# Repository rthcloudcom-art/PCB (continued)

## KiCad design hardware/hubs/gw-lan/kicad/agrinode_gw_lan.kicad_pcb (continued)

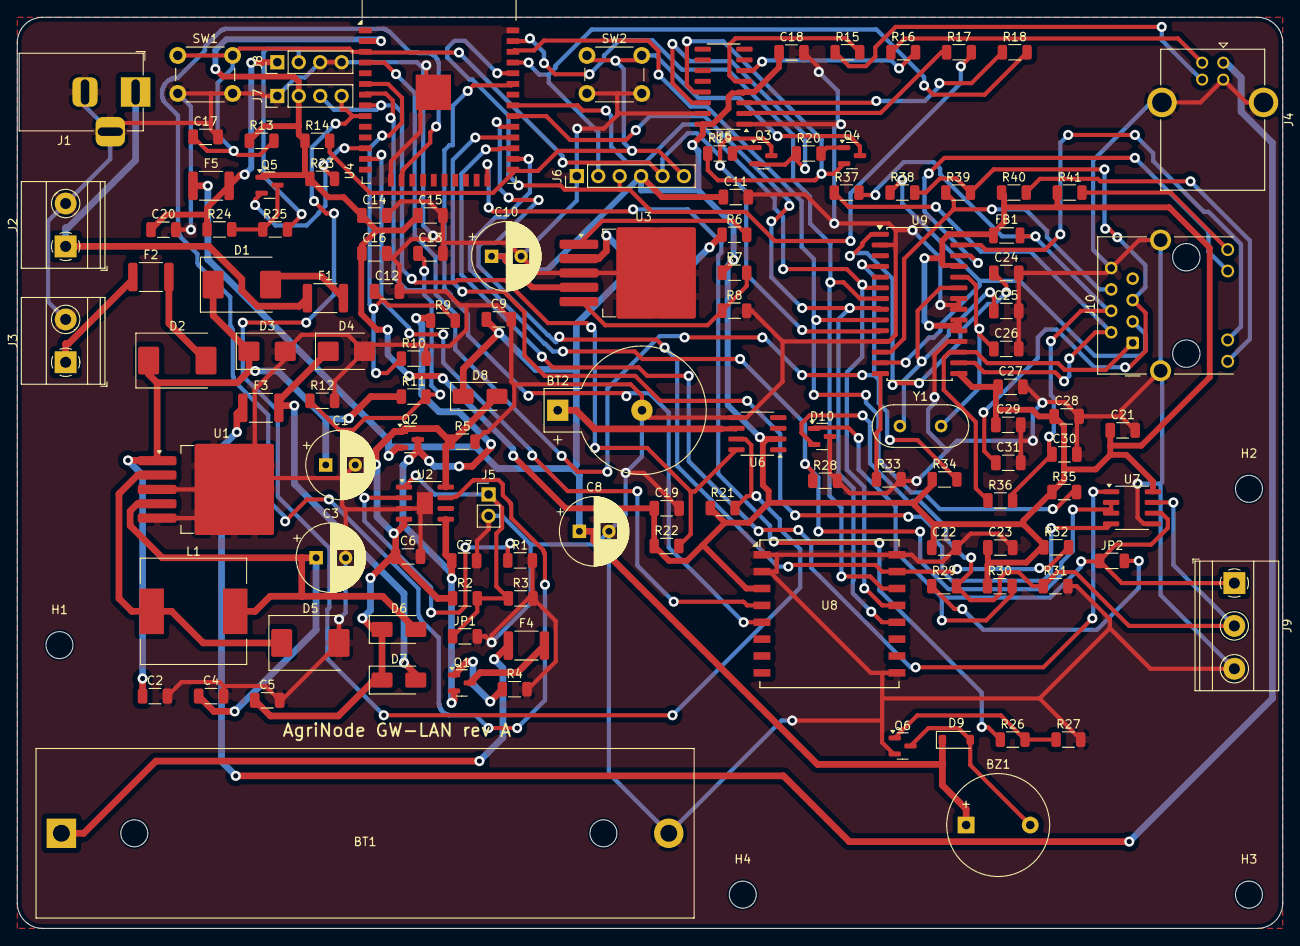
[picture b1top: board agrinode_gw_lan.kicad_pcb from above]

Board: 2 copper layers, 150.0 x 108.0 mm, 126 parts (0 on the bottom side), 76 nets.

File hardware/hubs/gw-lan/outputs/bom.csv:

Qty,Value,Footprint,Symbol,Option,References
1,18650 Li-ion (protected),BatteryHolder_MPD_BH-18650-PC2,Device:Battery_Cell,CORE,BT1
1,CR2032,BatteryHolder_Keystone_500,Device:Battery_Cell,CORE,BT2
1,5V magnetic buzzer,Buzzer_12x9.5RM7.6,Device:Buzzer,CORE,BZ1
1,220u/35V,CP_Radial_D8.0mm_P3.50mm,Device:C_Polarized,CORE,C1
1,1u/50V,C_1206_3216Metric,Device:C,CORE,C2
2,220u/10V,CP_Radial_D8.0mm_P3.50mm,Device:C_Polarized,CORE,C3 C8
3,1u,C_1206_3216Metric,Device:C,CORE,C4 C11 C17
7,10u,C_1206_3216Metric,Device:C,CORE,C5 C6 C7 C9 C22 C24 C27
1,100u/10V,CP_Radial_D8.0mm_P3.50mm,Device:C_Polarized,CORE,C10
11,100n,C_1206_3216Metric,Device:C,CORE,C12 C13 C15 C16 C18 C19 C23 C28 C29 C30 C31
2,22u,C_1206_3216Metric,Device:C,CORE,C14 C20
1,100n,C_1206_3216Metric,Device:C,RS485,C21
2,18p,C_1206_3216Metric,Device:C,CORE,C25 C26
3,SS54 40V/5A,D_SMC,Device:D_Schottky,CORE,D1 D2 D5
1,SMBJ24CA,D_SMB,Device:D_TVS,CORE,D3
1,SMBJ6.0CA,D_SMB,Device:D_TVS,CORE,D4
3,SS34,D_SMA,Device:D_Schottky,CORE,D6 D7 D8
1,1N4148W,D_SOD-123,Device:D,CORE,D9
1,SM712,SOT-23,Diode:SM712_SOT23,RS485,D10
2,PTC 1.5A/30V,Fuse_1812_4532Metric,Device:Polyfuse,CORE,F1 F2
1,PTC 1.5A/8V,Fuse_1812_4532Metric,Device:Polyfuse,CORE,F3
1,PTC 3A/16V,Fuse_1812_4532Metric,Device:Polyfuse,CORE,F4
1,PTC 0.75A/16V,Fuse_1812_4532Metric,Device:Polyfuse,CORE,F5
1,600R@100MHz,L_1206_3216Metric,Device:FerriteBead_Small,CORE,FB1
4,M3,MountingHole_3.2mm_M3,Mechanical:MountingHole,CORE,H1 H2 H3 H4
1,DC 12V 5.5/2.1,BarrelJack_Horizontal,Connector:Barrel_Jack_Switch,CORE,J1
1,DC IN 7-24V,"TerminalBlock_Phoenix_MKDS-1,5-2-5.08_1x02_P5.08mm_Horizontal",Connector:Screw_Terminal_01x02,CORE,J2
1,SOLAR 6-24V,"TerminalBlock_Phoenix_MKDS-1,5-2-5.08_1x02_P5.08mm_Horizontal",Connector:Screw_Terminal_01x02,CORE,J3
1,USB 5V / PROG,USB_B_THT_Coarse,Connector:USB_B,CORE,J4
1,BAT NTC 10k,PinHeader_1x02_P2.54mm_Vertical,Connector_Generic:Conn_01x02,CORE,J5
1,PROG,PinHeader_1x06_P2.54mm_Vertical,Connector_Generic:Conn_01x06,CORE,J6
1,I2C,PinHeader_1x04_P2.54mm_Vertical,Connector_Generic:Conn_01x04,CORE,J7
1,LED STRIP WS2813,PinHeader_1x04_P2.54mm_Vertical,Connector_Generic:Conn_01x04,CORE,J8
1,RS-485,"TerminalBlock_Phoenix_MKDS-1,5-3-5.08_1x03_P5.08mm_Horizontal",Connector:Screw_Terminal_01x03,RS485,J9
1,LAN,RJ45_Hanrun_HR911105A_Horizontal,Connector:RJ45_Hanrun_HR911105A_Horizontal,CORE,J10
1,0R JP_NTC (fit if no NTC),R_1206_3216Metric,Device:R,CORE,JP1
1,0R TERM (end of line),R_1206_3216Metric,Device:R,RS485,JP2
1,33uH 3A,L_12x12mm_H6mm,Device:L,CORE,L1
2,AO3401A,SOT-23,Transistor_FET:AO3401A,CORE,Q1 Q2
3,MMBT3904,SOT-23,Device:Q_NPN_BEC,CORE,Q3 Q4 Q6
1,BSS138,SOT-23,Transistor_FET:BSS138,CORE,Q5
1,1.2k,R_1206_3216Metric,Device:R,CORE,R1
1,5.6k,R_1206_3216Metric,Device:R,CORE,R2
1,75k,R_1206_3216Metric,Device:R,CORE,R3
4,1k,R_1206_3216Metric,Device:R,CORE,R4 R17 R18 R26
1,100k,R_1206_3216Metric,Device:R,CORE,R5
1,47k,R_1206_3216Metric,Device:R,CORE,R6
1,16.5k 1%,R_1206_3216Metric,Device:R,CORE,R7
1,10k 1%,R_1206_3216Metric,Device:R,CORE,R8
2,100k 1%,R_1206_3216Metric,Device:R,CORE,R9 R10
1,330k 1%,R_1206_3216Metric,Device:R,CORE,R11
1,47k 1%,R_1206_3216Metric,Device:R,CORE,R12
8,10k,R_1206_3216Metric,Device:R,CORE,R13 R14 R19 R20 R27 R32 R34 R35
2,22,R_1206_3216Metric,Device:R,CORE,R15 R16
3,4.7k,R_1206_3216Metric,Device:R,CORE,R21 R22 R23
1,2.2k,R_1206_3216Metric,Device:R,CORE,R24
3,330,R_1206_3216Metric,Device:R,CORE,R25 R40 R41
1,10k,R_1206_3216Metric,Device:R,RS485,R28
1,120,R_1206_3216Metric,Device:R,RS485,R29
2,680,R_1206_3216Metric,Device:R,RS485,R30 R31
1,2.32k 1%,R_1206_3216Metric,Device:R,CORE,R33
4,49.9 1%,R_1206_3216Metric,Device:R,CORE,R36 R37 R38 R39
1,RESET,SW_PUSH_6mm,Switch:SW_Push,CORE,SW1
1,BOOT / PAIR,SW_PUSH_6mm,Switch:SW_Push,CORE,SW2
1,LM2596S-5.0,TO-263-5_TabPin3,Regulator_Switching:LM2596S-5,CORE,U1
1,TP4056,ESOP-8_TP4056_Coarse,agrinode:TP4056,CORE,U2
1,MIC29302WU,TO-263-5_TabPin3,Regulator_Linear:MIC29302WU,CORE,U3
1,ESP32-WROOM-32E-N8,ESP32-WROOM-32E_Coarse,RF_Module:ESP32-WROOM-32E,CORE,U4
1,CH340C,SOIC-16_3.9x9.9mm_P1.27mm,Interface_USB:CH340C,CORE,U5
1,DS3231MZ,SOIC-8_3.9x4.9mm_P1.27mm,Timer_RTC:DS3231MZ,CORE,U6
1,MAX3485ESA,SOIC-8_3.9x4.9mm_P1.27mm,Interface_UART:MAX3485,RS485,U7
1,Ra-02 SX1278 433MHz,Ai-Thinker-Ra-02_Coarse,RF_Module:Ai-Thinker-Ra-02,CORE,U8
1,ENC28J60-I/SO,SOIC-28W_7.5x17.9mm_P1.27mm,Interface_Ethernet:ENC28J60x-SO,CORE,U9
1,25MHz,Crystal_HC49-4H_Vertical,Device:Crystal,CORE,Y1

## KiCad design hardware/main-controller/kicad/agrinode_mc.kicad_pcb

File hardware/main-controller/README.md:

# AgriNode MC-1 — برد کنترلر اصلی (rev A)

برد مرکزی سیستم برای گلخانه، مرغداری، دامداری، پرورش ماهی و مزرعه/باغ.
معماری کلی در [`docs/02-architecture.md`](../../docs/02-architecture.md).

## فایل‌ها

| مسیر | توضیح |
|---|---|
| `design/main_controller.py` | **منبع اصلی طراحی** (مدار به صورت کد پایتون) |
| `build.py` | تولید شماتیک KiCad، بررسی نت‌لیست، BOM و PDF |
| `pcb.py` | تولید PCB (چیدمان، لایه‌ها، کلاس نت‌ها، زون‌ها)؛ `--route` مسیریابی با Freerouting |
| `kicad/` | پروژه‌ی KiCad (باز شود با KiCad 7 یا جدیدتر) |
| `outputs/agrinode_mc_schematic.pdf` | شماتیک PDF |
| `outputs/bom.csv` | لیست قطعات |
| `outputs/drc.rpt` | گزارش DRC |
| `outputs/pcb_routed.png` | تصویر برد مسیریابی‌شده |
| `outputs/route/agrinode_mc.ses` | خروجی Freerouting (برای `pcb.py --import-ses`) |

## وضعیت PCB (rev A)

- چیدمان کامل، بدون تداخل Courtyard؛ 4 لایه (In1=GND، In2=+3V3)
- مسیریابی خودکار Freerouting (15 پاس): 3083 سگمنت ترک، 626 ویا
- DRC: **0 خطای فاصله (clearance)**، 48 پد متصل‌نشده (عمدتاً اتصال پدهای +3V3/GND به صفحه‌های داخلی و چند سیگنال) که باید دستی کامل شوند
- باقی موارد DRC هشدارهای سیلک‌اسکرین و thermal است
- ترک‌های کنتاکت رله (10A/250VAC) با عرض 2.5mm روی هر دو لایه‌ی بیرونی

```bash
python3 build.py         # شماتیک + نت‌لیست + BOM + PDF
python3 pcb.py --route   # PCB + مسیریابی خودکار (نیاز به Java 25 و freerouting.jar)
```

> شماتیک و PCB **از روی کد تولید می‌شوند**؛ برای تغییر مدار، `design/main_controller.py` را ویرایش و
> دوباره build کنید. بعد از شروع ویرایش دستی layout در KiCad، دیگر `pcb.py` را اجرا نکنید
> (برای همگام‌سازی از Update PCB from Schematic — F8 — استفاده کنید؛ مسیر UUIDها ثابت است).

## مشخصات

| مورد | مقدار |
|---|---|
| ابعاد | 240 × 180 mm، 4 لایه، 4 سوراخ M3 |
| تغذیه | 9-32V DC (نامی 24V) + ورودی باتری پشتیبان، diode-OR، فیوز PTC، TVS 33V |
| مصرف | حدود 1.5W بی‌بار؛ تا 6W با 8 رله روشن و مودم فعال |
| پردازنده | ESP32-S3 (240MHz دو هسته، 16MB Flash، 2MB PSRAM)، Wi-Fi 4 + BLE 5 |
| ارتباط | Ethernet 10/100، LoRa 433MHz، اسلات مودم 2G/4G، USB-C، 2× RS-485 |
| خروجی | 8 رله 10A/250VAC (NO/C/NC)، 4 MOSFET سمت پایین 2A با PWM، 2 آنالوگ 0-10V |
| ورودی | 8 دیجیتال ایزوله 10-32V AC/DC (DI1/DI2 شمارنده‌ی پالس)، 4 آنالوگ 16 بیت 0-10V/4-20mA |
| باس سنسور | 1-Wire (DS18B20)، I²C خارجی، RS-485 ایزوله (Modbus) |
| محلی | OLED I²C، 4 دکمه، 3 LED وضعیت، بازر، RTC با باتری، microSD |

## نقشه‌ی پایه‌های ESP32-S3

| GPIO | سیگنال | GPIO | سیگنال |
|---|---|---|---|
| 0 | BOOT / دکمه‌ی OK | 21 | OUT1 (PWM) |
| 1 | VIN_MAIN_SENSE (ADC، تشخیص قطع برق) | 35 | WDT_WAKE |
| 2 | VIN_BAT_SENSE (ADC) | 36 | MODEM_RI |
| 3 | OUT3 (PWM) | 37 | BUZZER |
| 4 / 5 | I²C SDA / SCL | 38 / 39 / 40 | RS485-A TX / RX / DE |
| 6 | EXP_INT (وقفه‌ی دو PCA9555) | 41 / 42 / 47 | RS485-B TX / RX / DE |
| 7 / 8 | DI1 / DI2 (شمارنده پالس PCNT) | 43 / 44 | MODEM TXD / RXD (UART0) |
| 9 / 10 / 11 | SPI SCK / MOSI / MISO | 45 | OUT4 (PWM، پایه‌ی Strap با pull-down) |
| 12 / 13 | ETH_CS / ETH_INT | 46 | LED STATUS (Strap) |
| 14 | WDT_DONE | 48 | OUT2 (PWM) |
| 15 / 16 | LORA_CS / LORA_DIO0 | 19 / 20 | USB D- / D+ (کنسول و پروگرام) |
| 17 | SD_CS | 18 | 1-Wire |

کنسول دیباگ از طریق USB-Serial-JTAG داخلی است (UART0 به مودم اختصاص دارد).

## آدرس‌های I²C

| آدرس | قطعه | کاربرد |
|---|---|---|
| 0x20 | PCA9555 #1 | IO0: رله 1..8 · IO1: ورودی دیجیتال 1..8 |
| 0x21 | PCA9555 #2 | IO0: ETH_RST, LORA_RST, MODEM_PWRKEY, MODEM_RST, LED_NET, LED_ALARM, SD_CD, MODEM_STATUS · IO1: BTN_UP/DOWN/BACK, RTC_INT, LORA_DIO1, SPARE 5..7 |
| 0x48 | ADS1115 | AI1..AI4 |
| 0x60 | MCP4728 | AO1, AO2 (کانال A/B) |
| 0x68 | DS3231M | RTC |
| 0x35 | ATECC608B-TNGTLS | عنصر امن (نسخه‌ی TNGTLS انتخاب شد تا با MCP4728 در 0x60 تداخل نکند) |
| 0x3C | OLED | نمایشگر |

## ترمینال‌ها (Phoenix MSTB 5.08mm)

| ترمینال | پایه‌ها |
|---|---|
| MAIN IN / BATTERY IN | + ، GND |
| RELAY 1..8 | NO ، COM ، NC |
| DI 1-4 / DI 5-8 | DI×4 ، COM (COM به + یا − منبع ورودی) |
| AI 1-2 / AI 3-4 | VSENS(24V تغذیه‌ی ترنسمیتر) ، AIx ، AIy ، GND |
| AO 1-2 | AO1 ، AO2 ، GND |
| OUT 1-2 / OUT 3-4 | VFIELD(+24V) ، OUTx ، OUTy (بار بین +24V و OUT) |
| RS485-A EXP BUS | +24V ، A ، B ، GND |
| RS485-B FIELD | A ، B ، GND_ISO |
| 1-WIRE | 3V3 ، DQ ، GND |
| I2C EXT | 3V3 ، SDA ، SCL ، GND |

## مواردی که پیش از سفارش ساخت باید بازبینی شوند

1. هنگام خرید، ATECC608B حتماً نسخه‌ی **TNGTLS** باشد (آدرس 0x35)؛ نسخه‌ی معمولی 0x60 با MCP4728 تداخل دارد.
2. مقادیر جبران‌ساز TPS54360 (R/C روی COMP) با WEBENCH یا محاسبات دیتاشیت تأیید شود.
3. مدار ترمینیشن W5500 با طرح مرجع WIZnet مطابقت داده شود.
4. مقاومت DELAY واچ‌داگ TPL5010 از جدول دیتاشیت برای زمان دلخواه انتخاب شود.
5. شکاف (slot) فرزکاری زیر رله‌ها برای افزایش فاصله‌ی خزشی 250VAC اضافه شود.
6. ERC کامل در KiCad 8/9 (نسخه‌ی 7 خط فرمان ERC ندارد؛ اتصالات با نت‌لیست خود KiCad تطبیق داده شده‌اند).
7. 48 اتصال باقی‌مانده را دستی کامل کنید. مسیریابی خودکار فقط نقطه‌ی شروع است: مسیرهای سوییچینگ بک‌ها، کریستال W5500 و جفت‌های
   دیفرانسیل USB/Ethernet باید دستی بازبینی و بهینه شوند.

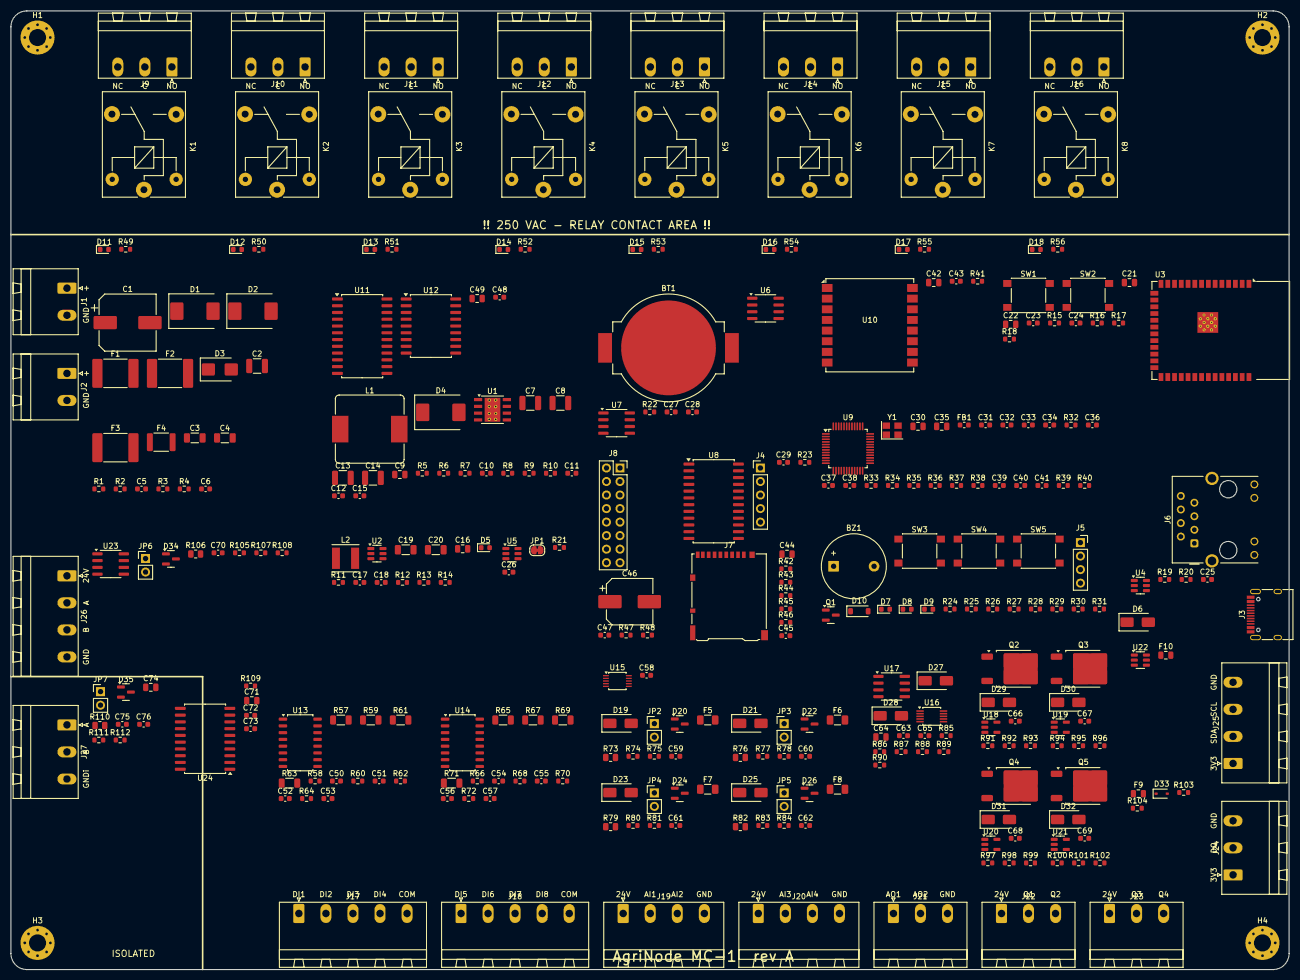
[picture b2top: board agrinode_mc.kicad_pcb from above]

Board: 4 copper layers, 240.0 x 180.0 mm, 319 parts (0 on the bottom side), 223 nets, no tracks yet.

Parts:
BT1: CR2032; BatteryHolder_MPD_BC2003_1x2032
BZ1: 5V magnetic buzzer; Buzzer_12x9.5RM7.6
C1: 100u/50V; CP_Elec_10x10.5
C2, C7, C8: 2.2u/100V; C_1210_3225Metric
C3, C4: 1u/50V; C_1206_3216Metric
C5, C6, C10, C15, C17, C18, C23, C26, C27, C28, C29, C31, C32, C33, C34, C41, C43, C45, C47, C48, C58, C59, C60, C61, C62, C63, C66, C67, C68, C69, C70, C72, C73, C75, C76: 100n; C_0603_1608Metric
C9: 100n/100V; C_0805_2012Metric
C11, C39: 6.8n; C_0603_1608Metric
C12: 33p; C_0603_1608Metric
C13, C14: 47u/10V; C_1210_3225Metric
C16, C22, C30, C42, C44, C49, C64, C71, C74: 10u/10V; C_0805_2012Metric
C19, C20: 22u/10V; C_1206_3216Metric
C21: 22u/10V; C_0805_2012Metric
C24: 1u; C_0603_1608Metric
C25: 1u/16V; C_0603_1608Metric
C35: 4.7u; C_0805_2012Metric
C36, C40: 10n; C_0603_1608Metric
C37, C38: 18p; C_0603_1608Metric
C46: 470u/10V; CP_Elec_8x10.5
C50, C51, C52, C53, C54, C55, C56, C57: 1n; C_0603_1608Metric
C65: 100n/50V; C_0603_1608Metric
D1, D2: SS510 100V/5A; D_SMC
D3: SMBJ33CA; D_SMB
D4: B560C 60V/5A; D_SMC
D5: LED green PWR; LED_0603_1608Metric
D6: SS34; D_SMA
D7: LED blue STATUS; LED_0603_1608Metric
D8: LED green NET; LED_0603_1608Metric
D9: LED red ALARM; LED_0603_1608Metric
D10: 1N4148W; D_SOD-123
D11: LED red K1; LED_0603_1608Metric
D12: LED red K2; LED_0603_1608Metric
D13: LED red K3; LED_0603_1608Metric
D14: LED red K4; LED_0603_1608Metric
D15: LED red K5; LED_0603_1608Metric
D16: LED red K6; LED_0603_1608Metric
D17: LED red K7; LED_0603_1608Metric
D18: LED red K8; LED_0603_1608Metric
D19, D21, D23, D25, D27, D28: SMAJ12CA; D_SMA
D20, D22, D24, D26: BAT54S; SOT-23
D29, D30, D31, D32: SS26 60V/2A; D_SMA
D33: PESD5V0S1BL; D_SOD-323
D34, D35: SM712; SOT-23
F1, F2: PTC 2.5A/60V 2920; Fuse_2920_7451Metric
F3: PTC 3A/60V 2920; Fuse_2920_7451Metric
F4: PTC 0.5A/60V 1812; Fuse_1812_4532Metric
F5, F6, F7, F8: PTC 50mA/30V; Fuse_1206_3216Metric
F9, F10: PTC 100mA; Fuse_0805_2012Metric
FB1: 600R@100MHz; L_0603_1608Metric
H1, H2, H3, H4: M3; MountingHole_3.2mm_M3_Pad_Via
J1: MAIN IN 9-32V; PhoenixContact_MSTBA_2,5_2-G-5,08_1x02_P5.08mm_Horizontal
J2: BATTERY IN 9-32V; PhoenixContact_MSTBA_2,5_2-G-5,08_1x02_P5.08mm_Horizontal
J3: USB-C; USB_C_Receptacle_HRO_TYPE-C-31-M-12
J4: SPARE IO; PinHeader_1x05_P2.54mm_Vertical
J5: OLED I2C; PinSocket_1x04_P2.54mm_Vertical
J6: ETHERNET; RJ45_Hanrun_HR911105A_Horizontal
J7: microSD; microSD_HC_Hirose_DM3AT-SF-PEJM5
J8: MODEM SLOT; PinSocket_2x08_P2.54mm_Vertical
J9: RELAY 1; PhoenixContact_MSTBA_2,5_3-G-5,08_1x03_P5.08mm_Horizontal
J10: RELAY 2; PhoenixContact_MSTBA_2,5_3-G-5,08_1x03_P5.08mm_Horizontal
J11: RELAY 3; PhoenixContact_MSTBA_2,5_3-G-5,08_1x03_P5.08mm_Horizontal
J12: RELAY 4; PhoenixContact_MSTBA_2,5_3-G-5,08_1x03_P5.08mm_Horizontal
J13: RELAY 5; PhoenixContact_MSTBA_2,5_3-G-5,08_1x03_P5.08mm_Horizontal
J14: RELAY 6; PhoenixContact_MSTBA_2,5_3-G-5,08_1x03_P5.08mm_Horizontal
J15: RELAY 7; PhoenixContact_MSTBA_2,5_3-G-5,08_1x03_P5.08mm_Horizontal
J16: RELAY 8; PhoenixContact_MSTBA_2,5_3-G-5,08_1x03_P5.08mm_Horizontal
J17: DI 1-4; PhoenixContact_MSTBA_2,5_5-G-5,08_1x05_P5.08mm_Horizontal
J18: DI 5-8; PhoenixContact_MSTBA_2,5_5-G-5,08_1x05_P5.08mm_Horizontal
J19: AI 1-2; PhoenixContact_MSTBA_2,5_4-G-5,08_1x04_P5.08mm_Horizontal
J20: AI 3-4; PhoenixContact_MSTBA_2,5_4-G-5,08_1x04_P5.08mm_Horizontal
J21: AO 1-2; PhoenixContact_MSTBA_2,5_3-G-5,08_1x03_P5.08mm_Horizontal
J22: OUT 1-2; PhoenixContact_MSTBA_2,5_3-G-5,08_1x03_P5.08mm_Horizontal
J23: OUT 3-4; PhoenixContact_MSTBA_2,5_3-G-5,08_1x03_P5.08mm_Horizontal
J24: 1-WIRE; PhoenixContact_MSTBA_2,5_3-G-5,08_1x03_P5.08mm_Horizontal
J25: I2C EXT; PhoenixContact_MSTBA_2,5_4-G-5,08_1x04_P5.08mm_Horizontal
J26: RS485-A EXP BUS; PhoenixContact_MSTBA_2,5_4-G-5,08_1x04_P5.08mm_Horizontal
J27: RS485-B FIELD; PhoenixContact_MSTBA_2,5_3-G-5,08_1x03_P5.08mm_Horizontal
JP1: WDT_EN; SolderJumper-2_P1.3mm_Bridged_RoundedPad1.0x1.5mm
JP2, JP3, JP4, JP5: 4-20mA; PinHeader_1x02_P2.54mm_Vertical
JP6: TERM A; PinHeader_1x02_P2.54mm_Vertical
JP7: TERM B; PinHeader_1x02_P2.54mm_Vertical
K1, K2, K3, K4, K5, K6, K7, K8: SRD-05VDC-SL-C; Relay_SPDT_SANYOU_SRD_Series_Form_C
L1: 10uH 6A SRP1245A-100M; L_Bourns_SRP1245A
L2: 2.2uH 4A NR5040; L_Taiyo-Yuden_NR-50xx
Q1: MMBT3904; SOT-23
Q2, Q3, Q4, Q5: IRLR2905; TO-252-2
R1, R3: 150k 1%; R_0603_1608Metric
R2, R4, R13, R86, R89: 10k 1%; R_0603_1608Metric
R5: 294k 1%; R_0603_1608Metric
R6: 46.4k 1%; R_0603_1608Metric
R7: 243k 1%; R_0603_1608Metric
R8: 53.6k 1%; R_0603_1608Metric
R9: 10.2k 1%; R_0603_1608Metric
R10: 16.9k; R_0603_1608Metric
R11, R91, R93, R94, R96, R97, R99, R100, R102: 100k; R_0603_1608Metric
R12: 33.2k 1%; R_0603_1608Metric
R14, R27, R28, R29, R30: 1k; R_0603_1608Metric
R15, R16, R17, R18, R22, R23, R24, R25, R26, R31, R33, R34, R41, R42, R43, R44, R45, R46, R47, R48, R58, R60, R62, R64, R66, R68, R70, R72, R105, R109: 10k; R_0603_1608Metric
R19, R20: 5.1k; R_0603_1608Metric
R21: 57.6k 1%; R_0603_1608Metric
R32: 12.4k 1%; R_0603_1608Metric
R35, R36, R37, R38: 49.9 1%; R_0603_1608Metric
R39, R40: 330; R_0603_1608Metric
R49, R50, R51, R52, R53, R54, R55, R56: 2.2k; R_0603_1608Metric
R57, R59, R61, R63, R65, R67, R69, R71: 4.7k 1206; R_1206_3216Metric
R73, R76, R79, R82: 150 0.1%; R_0805_2012Metric
R74, R77, R80, R83: 30k 0.1%; R_0603_1608Metric
R75, R78, R81, R84: 10k 0.1%; R_0603_1608Metric
R85, R88: 39k 1%; R_0603_1608Metric
R87, R90: 100; R_0603_1608Metric
R92, R95, R98, R101, R104: 22; R_0603_1608Metric
R103: 4.7k; R_0603_1608Metric
R106, R110: 120; R_0805_2012Metric
R107, R108, R111, R112: 680; R_0603_1608Metric
SW1: RESET; SW_SPST_PTS645
SW2: BOOT / OK; SW_SPST_PTS645
SW3: UP; SW_SPST_PTS645
SW4: DOWN; SW_SPST_PTS645
SW5: BACK; SW_SPST_PTS645
U1: TPS54360DDA; TI_SO-PowerPAD-8_ThermalVias
U2: TPS563200; SOT-23-6
U3: ESP32-S3-WROOM-1-N16R2; ESP32-S3-WROOM-1
U4, U22: USBLC6-2SC6; SOT-23-6
U5: TPL5010; SOT-23-6
U6: DS3231MZ; SOIC-8_3.9x4.9mm_P1.27mm
U7: ATECC608B-TNGTLS (I2C 0x35); SOIC-8_3.9x4.9mm_P1.27mm
U8, U11: PCA9555D; SOIC-24W_7.5x15.4mm_P1.27mm
U9: W5500; LQFP-48_7x7mm_P0.5mm
U10: Ra-02 SX1278 433MHz; Ai-Thinker-Ra-01-LoRa
U12: ULN2803A; SOIC-18W_7.5x11.6mm_P1.27mm
U13, U14: TLP290-4; SOP-16_4.55x10.3mm_P1.27mm
U15: ADS1115IDGS; TSSOP-10_3x3mm_P0.5mm
U16: MCP4728; MSOP-10_3x3mm_P0.5mm
U17: OPA2196xD; SOIC-8_3.9x4.9mm_P1.27mm
U18, U19, U20, U21: 74AHCT1G125; SOT-23-5
U23: THVD1420D; SOIC-8_3.9x4.9mm_P1.27mm
U24: ADM2587E; SOIC-20W_7.5x12.8mm_P1.27mm
Y1: 25MHz 18pF; Crystal_SMD_3225-4Pin_3.2x2.5mm

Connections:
+3V3: C19.1, C20.1, C21.1, C22.1, C23.1, C26.1, C27.1, C28.1, C29.1, C34.1, C42.1, C43.1, C44.1, C45.1, C48.1, C58.1, C63.1, C64.1, C70.1, C71.1, C72.1, C73.1, D20.2, D22.2, D24.2, D26.2, F9.1, F10.1, FB1.1, J4.1, J5.2, J7.4, J8.11, L2.2, R12.1, R14.1, R15.1, R16.1, R17.1, R18.1, R22.1, R23.1, R24.1, R25.1, R26.1, R28.1, R29.1, R33.1, R34.1, R39.1, R40.1, R41.1, R42.1, R43.1, R44.1, R45.1, R46.1, R48.1, R58.1, R60.1, R62.1, R64.1, R66.1, R68.1, R70.1, R72.1, R103.1, R107.1, U3.2, U5.1, U6.2, U7.8, U8.21, U8.24, U9.28, U9.43, U9.44, U9.45, U10.3, U11.24, U15.8, U16.1, U22.5, U23.8, U24.2, U24.8
+5V: BZ1.1, C13.1, C14.1, C15.1, C16.1, C17.1, C46.1, C47.1, C49.1, C66.1, C67.1, C68.1, C69.1, D6.1, D10.1, J8.1, J8.2, J8.16, K1.2, K2.2, K3.2, K4.2, K5.2, K6.2, K7.2, K8.2, L1.2, R8.1, R11.1, R49.1, R50.1, R51.1, R52.1, R53.1, R54.1, R55.1, R56.1, U2.3, U12.10, U18.5, U19.5, U20.5, U21.5
/Analog IO, MOSFET outputs, 1-Wire, ext. I2C/AI1_ADC: C59.1, D20.3, R74.2, R75.1, U15.4
/Analog IO, MOSFET outputs, 1-Wire, ext. I2C/AI1_IN: D19.1, F5.2, JP2.1, R74.1
/Analog IO, MOSFET outputs, 1-Wire, ext. I2C/AI1_SH: JP2.2, R73.1
/Analog IO, MOSFET outputs, 1-Wire, ext. I2C/AI1_T: F5.1, J19.2
/Analog IO, MOSFET outputs, 1-Wire, ext. I2C/AI2_ADC: C60.1, D22.3, R77.2, R78.1, U15.5
/Analog IO, MOSFET outputs, 1-Wire, ext. I2C/AI2_IN: D21.1, F6.2, JP3.1, R77.1
/Analog IO, MOSFET outputs, 1-Wire, ext. I2C/AI2_SH: JP3.2, R76.1
/Analog IO, MOSFET outputs, 1-Wire, ext. I2C/AI2_T: F6.1, J19.3
/Analog IO, MOSFET outputs, 1-Wire, ext. I2C/AI3_ADC: C61.1, D24.3, R80.2, R81.1, U15.6
/Analog IO, MOSFET outputs, 1-Wire, ext. I2C/AI3_IN: D23.1, F7.2, JP4.1, R80.1
/Analog IO, MOSFET outputs, 1-Wire, ext. I2C/AI3_SH: JP4.2, R79.1
/Analog IO, MOSFET outputs, 1-Wire, ext. I2C/AI3_T: F7.1, J20.2
/Analog IO, MOSFET outputs, 1-Wire, ext. I2C/AI4_ADC: C62.1, D26.3, R83.2, R84.1, U15.7
/Analog IO, MOSFET outputs, 1-Wire, ext. I2C/AI4_IN: D25.1, F8.2, JP5.1, R83.1
/Analog IO, MOSFET outputs, 1-Wire, ext. I2C/AI4_SH: JP5.2, R82.1
/Analog IO, MOSFET outputs, 1-Wire, ext. I2C/AI4_T: F8.1, J20.3
/Analog IO, MOSFET outputs, 1-Wire, ext. I2C/AO1_DAC: U16.6, U17.3
/Analog IO, MOSFET outputs, 1-Wire, ext. I2C/AO1_FB: R85.2, R86.1, U17.2
/Analog IO, MOSFET outputs, 1-Wire, ext. I2C/AO1_OUT: R85.1, R87.1, U17.1
/Analog IO, MOSFET outputs, 1-Wire, ext. I2C/AO1_T: D27.1, J21.1, R87.2
/Analog IO, MOSFET outputs, 1-Wire, ext. I2C/AO2_DAC: U16.7, U17.5
/Analog IO, MOSFET outputs, 1-Wire, ext. I2C/AO2_FB: R88.2, R89.1, U17.6
/Analog IO, MOSFET outputs, 1-Wire, ext. I2C/AO2_OUT: R88.1, R90.1, U17.7
/Analog IO, MOSFET outputs, 1-Wire, ext. I2C/AO2_T: D28.1, J21.2, R90.2
/Analog IO, MOSFET outputs, 1-Wire, ext. I2C/ONEWIRE_T: D33.1, J24.2, R104.2
/Analog IO, MOSFET outputs, 1-Wire, ext. I2C/OUT1: D29.2, J22.2, Q2.2
/Analog IO, MOSFET outputs, 1-Wire, ext. I2C/OUT1_DRV: R92.1, U18.4
/Analog IO, MOSFET outputs, 1-Wire, ext. I2C/OUT1_G: Q2.1, R92.2, R93.1
/Analog IO, MOSFET outputs, 1-Wire, ext. I2C/OUT2: D30.2, J22.3, Q3.2
/Analog IO, MOSFET outputs, 1-Wire, ext. I2C/OUT2_DRV: R95.1, U19.4
/Analog IO, MOSFET outputs, 1-Wire, ext. I2C/OUT2_G: Q3.1, R95.2, R96.1
/Analog IO, MOSFET outputs, 1-Wire, ext. I2C/OUT3: D31.2, J23.2, Q4.2
/Analog IO, MOSFET outputs, 1-Wire, ext. I2C/OUT3_DRV: R98.1, U20.4
/Analog IO, MOSFET outputs, 1-Wire, ext. I2C/OUT3_G: Q4.1, R98.2, R99.1
/Analog IO, MOSFET outputs, 1-Wire, ext. I2C/OUT4: D32.2, J23.3, Q5.2
/Analog IO, MOSFET outputs, 1-Wire, ext. I2C/OUT4_DRV: R101.1, U21.4
/Analog IO, MOSFET outputs, 1-Wire, ext. I2C/OUT4_G: Q5.1, R101.2, R102.1
/Analog IO, MOSFET outputs, 1-Wire, ext. I2C/V_1W: F9.2, J24.1
/Analog IO, MOSFET outputs, 1-Wire, ext. I2C/V_I2C: F10.2, J25.1
/Ethernet, LoRa, microSD, Cellular slot/+3V3A: C30.1, C31.1, C32.1, C33.1, C41.1, FB1.2, J6.4, R35.2, R36.2, U9.4, U9.8, U9.11, U9.15, U9.17, U9.21
/Ethernet, LoRa, microSD, Cellular slot/ETH_1V2: C36.1, U9.22
/Ethernet, LoRa, microSD, Cellular slot/ETH_ACT: J6.11, U9.27
/Ethernet, LoRa, microSD, Cellular slot/ETH_EXRES: R32.1, U9.10
/Ethernet, LoRa, microSD, Cellular slot/ETH_LEDG_A: J6.9, R39.2
/Ethernet, LoRa, microSD, Cellular slot/ETH_LEDY_A: J6.12, R40.2
/Ethernet, LoRa, microSD, Cellular slot/ETH_LINK: J6.10, U9.25
/Ethernet, LoRa, microSD, Cellular slot/ETH_RCT: C40.1, J6.5
/Ethernet, LoRa, microSD, Cellular slot/ETH_RXBIAS: C39.1, R37.2, R38.2
/Ethernet, LoRa, microSD, Cellular slot/ETH_RXN: J6.6, R38.1, U9.5
/Ethernet, LoRa, microSD, Cellular slot/ETH_RXP: J6.3, R37.1, U9.6
/Ethernet, LoRa, microSD, Cellular slot/ETH_TOCAP: C35.1, U9.20
/Ethernet, LoRa, microSD, Cellular slot/ETH_TXN: J6.2, R36.1, U9.1
/Ethernet, LoRa, microSD, Cellular slot/ETH_TXP: J6.1, R35.1, U9.2
/Ethernet, LoRa, microSD, Cellular slot/ETH_XI: C37.1, U9.30, Y1.1
/Ethernet, LoRa, microSD, Cellular slot/ETH_XO: C38.1, U9.31, Y1.3
/Ethernet, LoRa, microSD, Cellular slot/SD_DAT1: J7.8, R44.2
/Ethernet, LoRa, microSD, Cellular slot/SD_DAT2: J7.1, R45.2
/MCU, USB, Watchdog, RTC, UI/BOOT_BTN: R16.2, SW2.1, U3.27
/MCU, USB, Watchdog, RTC, UI/BTN_BACK: R26.2, SW5.1, U8.15
/MCU, USB, Watchdog, RTC, UI/BTN_DOWN: R25.2, SW4.1, U8.14
/MCU, USB, Watchdog, RTC, UI/BTN_UP: R24.2, SW3.1, U8.13
/MCU, USB, Watchdog, RTC, UI/BUZZER_CTL: R30.1, U3.30
/MCU, USB, Watchdog, RTC, UI/BUZ_B: Q1.1, R30.2, R31.1
/MCU, USB, Watchdog, RTC, UI/BUZ_K: BZ1.2, D10.2, Q1.3
/MCU, USB, Watchdog, RTC, UI/ESP_EN: C24.1, JP1.2, R15.2, SW1.1, U3.3
/MCU, USB, Watchdog, RTC, UI/EXP_IO5: J4.2, U8.18
/MCU, USB, Watchdog, RTC, UI/EXP_IO6: J4.3, U8.19
/MCU, USB, Watchdog, RTC, UI/EXP_IO7: J4.4, U8.20
/MCU, USB, Watchdog, RTC, UI/LED_ALARM: D9.1, U8.9
/MCU, USB, Watchdog, RTC, UI/LED_ALARM_A: D9.2, R29.2
/MCU, USB, Watchdog, RTC, UI/LED_NET: D8.1, U8.8
/MCU, USB, Watchdog, RTC, UI/LED_NET_A: D8.2, R28.2
/MCU, USB, Watchdog, RTC, UI/LED_STATUS: R27.1, U3.16
/MCU, USB, Watchdog, RTC, UI/LED_STATUS_A: D7.2, R27.2
/MCU, USB, Watchdog, RTC, UI/RTC_INT: R22.2, U6.3, U8.16
/MCU, USB, Watchdog, RTC, UI/RTC_VBAT: BT1.1, U6.6
/MCU, USB, Watchdog, RTC, UI/USB_CC1: J3.A5, R19.1
/MCU, USB, Watchdog, RTC, UI/USB_CC2: J3.B5, R20.1
/MCU, USB, Watchdog, RTC, UI/USB_DN: J3.A7, J3.B7, U3.13, U4.3, U4.4
/MCU, USB, Watchdog, RTC, UI/USB_DP: J3.A6, J3.B6, U3.14, U4.1, U4.6
/MCU, USB, Watchdog, RTC, UI/WDT_DELAY: R21.1, U5.3
/MCU, USB, Watchdog, RTC, UI/WDT_DONE: U3.22, U5.4
/MCU, USB, Watchdog, RTC, UI/WDT_RST: JP1.1, U5.6
/MCU, USB, Watchdog, RTC, UI/WDT_WAKE: U3.28, U5.5
/Power Supply/BUCK3_BST: C18.1, U2.6
/Power Supply/BUCK3_EN: R11.2, U2.5
/Power Supply/BUCK3_FB: R12.2, R13.1, U2.4
/Power Supply/BUCK3_SW: C18.2, L2.1, U2.2
/Power Supply/BUCK5_BOOT: C10.1, U1.1
/Power Supply/BUCK5_CC: C11.1, R10.2
/Power Supply/BUCK5_COMP: C12.1, R10.1, U1.6
/Power Supply/BUCK5_EN: R5.2, R6.1, U1.3
/Power Supply/BUCK5_FB: R8.2, R9.1, U1.5
/Power Supply/BUCK5_RT: R7.1, U1.4
/Power Supply/BUCK5_SW: C10.2, D4.1, L1.1, U1.8
/Power Supply/PWR_LED_A: D5.2, R14.2
/Power Supply/VIN_BAT_F: D2.2, F2.2, R3.1
/Power Supply/VIN_BAT_RAW: F2.1, J2.1
/Power Supply/VIN_MAIN_F: D1.2, F1.2, R1.1
/Power Supply/VIN_MAIN_RAW: F1.1, J1.1
/Power Supply/VSYS: C1.1, C2.1, C7.1, C8.1, C9.1, D1.1, D2.1, D3.1, F3.1, F4.1, R5.1, U1.2
/RS-485 buses/GND_ISO: C74.2, C75.2, C76.2, D35.3, J27.3, R112.2, U24.11, U24.14, U24.16, U24.20
/RS-485 buses/RS485A_A: D34.1, J26.2, JP6.1, R107.2, U23.6
/RS-485 buses/RS485A_B: D34.2, J26.3, R106.2, R108.1, U23.7
/RS-485 buses/RS485A_TERM: JP6.2, R106.1
/RS-485 buses/RS485B_A: D35.1, J27.1, JP7.1, R111.2, U24.13, U24.18
/RS-485 buses/RS485B_B: D35.2, J27.2, R110.2, R112.1, U24.15, U24.17
/RS-485 buses/RS485B_TERM: JP7.2, R110.1
/RS-485 buses/VISO: C74.1, C75.1, C76.1, R111.1, U24.12, U24.19
/Relay outputs and isolated digital inputs/DI1_IN: J17.1, R57.1
/Relay outputs and isolated digital inputs/DI1_R: R57.2, U13.1
/Relay outputs and isolated digital inputs/DI2_IN: J17.2, R59.1
/Relay outputs and isolated digital inputs/DI2_R: R59.2, U13.3
/Relay outputs and isolated digital inputs/DI3: C52.1, R62.2, U11.15, U13.12
/Relay outputs and isolated digital inputs/DI3_IN: J17.3, R61.1
/Relay outputs and isolated digital inputs/DI3_R: R61.2, U13.5
/Relay outputs and isolated digital inputs/DI4: C53.1, R64.2, U11.16, U13.10
/Relay outputs and isolated digital inputs/DI4_IN: J17.4, R63.1
/Relay outputs and isolated digital inputs/DI4_R: R63.2, U13.7
/Relay outputs and isolated digital inputs/DI5: C54.1, R66.2, U11.17, U14.16
/Relay outputs and isolated digital inputs/DI5_IN: J18.1, R65.1
/Relay outputs and isolated digital inputs/DI5_R: R65.2, U14.1
/Relay outputs and isolated digital inputs/DI6: C55.1, R68.2, U11.18, U14.14
/Relay outputs and isolated digital inputs/DI6_IN: J18.2, R67.1
/Relay outputs and isolated digital inputs/DI6_R: R67.2, U14.3
/Relay outputs and isolated digital inputs/DI7: C56.1, R70.2, U11.19, U14.12
/Relay outputs and isolated digital inputs/DI7_IN: J18.3, R69.1
/Relay outputs and isolated digital inputs/DI7_R: R69.2, U14.5
/Relay outputs and isolated digital inputs/DI8: C57.1, R72.2, U11.20, U14.10
/Relay outputs and isolated digital inputs/DI8_IN: J18.4, R71.1
/Relay outputs and isolated digital inputs/DI8_R: R71.2, U14.7
/Relay outputs and isolated digital inputs/DI_COM1: J17.5, U13.2, U13.4, U13.6, U13.8
/Relay outputs and isolated digital inputs/DI_COM2: J18.5, U14.2, U14.4, U14.6, U14.8
/Relay outputs and isolated digital inputs/RLY1_COIL: D11.1, K1.5, U12.18
/Relay outputs and isolated digital inputs/RLY1_COM: J9.2, K1.1
/Relay outputs and isolated digital inputs/RLY1_CTL: U11.4, U12.1
/Relay outputs and isolated digital inputs/RLY1_LED: D11.2, R49.2
/Relay outputs and isolated digital inputs/RLY1_NC: J9.3, K1.4
/Relay outputs and isolated digital inputs/RLY1_NO: J9.1, K1.3
/Relay outputs and isolated digital inputs/RLY2_COIL: D12.1, K2.5, U12.17
/Relay outputs and isolated digital inputs/RLY2_COM: J10.2, K2.1
/Relay outputs and isolated digital inputs/RLY2_CTL: U11.5, U12.2
/Relay outputs and isolated digital inputs/RLY2_LED: D12.2, R50.2
/Relay outputs and isolated digital inputs/RLY2_NC: J10.3, K2.4
/Relay outputs and isolated digital inputs/RLY2_NO: J10.1, K2.3
/Relay outputs and isolated digital inputs/RLY3_COIL: D13.1, K3.5, U12.16
/Relay outputs and isolated digital inputs/RLY3_COM: J11.2, K3.1
/Relay outputs and isolated digital inputs/RLY3_CTL: U11.6, U12.3
/Relay outputs and isolated digital inputs/RLY3_LED: D13.2, R51.2
/Relay outputs and isolated digital inputs/RLY3_NC: J11.3, K3.4
/Relay outputs and isolated digital inputs/RLY3_NO: J11.1, K3.3
/Relay outputs and isolated digital inputs/RLY4_COIL: D14.1, K4.5, U12.15
/Relay outputs and isolated digital inputs/RLY4_COM: J12.2, K4.1
/Relay outputs and isolated digital inputs/RLY4_CTL: U11.7, U12.4
/Relay outputs and isolated digital inputs/RLY4_LED: D14.2, R52.2
/Relay outputs and isolated digital inputs/RLY4_NC: J12.3, K4.4
/Relay outputs and isolated digital inputs/RLY4_NO: J12.1, K4.3
/Relay outputs and isolated digital inputs/RLY5_COIL: D15.1, K5.5, U12.14
/Relay outputs and isolated digital inputs/RLY5_COM: J13.2, K5.1
/Relay outputs and isolated digital inputs/RLY5_CTL: U11.8, U12.5
/Relay outputs and isolated digital inputs/RLY5_LED: D15.2, R53.2
/Relay outputs and isolated digital inputs/RLY5_NC: J13.3, K5.4
/Relay outputs and isolated digital inputs/RLY5_NO: J13.1, K5.3
/Relay outputs and isolated digital inputs/RLY6_COIL: D16.1, K6.5, U12.13
/Relay outputs and isolated digital inputs/RLY6_COM: J14.2, K6.1
/Relay outputs and isolated digital inputs/RLY6_CTL: U11.9, U12.6
/Relay outputs and isolated digital inputs/RLY6_LED: D16.2, R54.2
/Relay outputs and isolated digital inputs/RLY6_NC: J14.3, K6.4
/Relay outputs and isolated digital inputs/RLY6_NO: J14.1, K6.3
/Relay outputs and isolated digital inputs/RLY7_COIL: D17.1, K7.5, U12.12
/Relay outputs and isolated digital inputs/RLY7_COM: J15.2, K7.1
/Relay outputs and isolated digital inputs/RLY7_CTL: U11.10, U12.7
/Relay outputs and isolated digital inputs/RLY7_LED: D17.2, R55.2
/Relay outputs and isolated digital inputs/RLY7_NC: J15.3, K7.4
/Relay outputs and isolated digital inputs/RLY7_NO: J15.1, K7.3
/Relay outputs and isolated digital inputs/RLY8_COIL: D18.1, K8.5, U12.11
/Relay outputs and isolated digital inputs/RLY8_COM: J16.2, K8.1
/Relay outputs and isolated digital inputs/RLY8_CTL: U11.11, U12.8
/Relay outputs and isolated digital inputs/RLY8_LED: D18.2, R56.2
/Relay outputs and isolated digital inputs/RLY8_NC: J16.3, K8.4
/Relay outputs and isolated digital inputs/RLY8_NO: J16.1, K8.3
DI1: C50.1, R58.2, U3.7, U11.13, U13.16
DI2: C51.1, R60.2, U3.12, U11.14, U13.14
ETH_CS: U3.20, U9.32
ETH_INT: R34.2, U3.21, U9.36
ETH_RST: R33.2, U8.4, U9.37
EXP_INT: R23.2, U3.6, U8.1, U11.1
GND: BT1.2, C1.2, C2.2, C3.2, C4.2, C5.2, C6.2, C7.2, C8.2, C9.2, C11.2, C12.2, C13.2, C14.2, C15.2, C16.2, C17.2, C19.2, C20.2, C21.2, C22.2, C23.2, C24.2, C25.2, C26.2, C27.2, C28.2, C29.2, C30.2, C31.2, C32.2, C33.2, C34.2, C35.2, C36.2, C37.2, C38.2, C39.2, C40.2, C41.2, C42.2, C43.2, C44.2, C45.2, C46.2, C47.2, C48.2, C49.2, C50.2, C51.2, C52.2, C53.2, C54.2, C55.2, C56.2, C57.2, C58.2, C59.2, C60.2, C61.2, C62.2, C63.2, C64.2, C65.2, C66.2, C67.2, C68.2, C69.2, C70.2, C71.2, C72.2, C73.2, D3.2, D4.2, D5.1, D7.1, D19.2, D20.1, D21.2, D22.1, D23.2, D24.1, D25.2, D26.1, D27.2, D28.2, D33.2, D34.3, H1.1, H2.1, H3.1, H4.1, J1.2, J2.2, J3.A1, J3.A12, J3.B1, J3.B12, J3.S1, J4.5, J5.1, J6.8, J6.SH, J7.6, J7.9, J7.11, J8.3, J8.4, J8.12, J8.15, J19.4, J20.4, J21.3, J24.3, J25.4, J26.4, Q1.2, Q2.3, Q3.3, Q4.3, Q5.3, R2.2, R4.2, R6.2, R7.2, R9.2, R13.2, R19.2, R20.2, R21.2, R31.2, R32.2, R47.2, R73.2, R75.2, R76.2, R78.2, R79.2, R81.2, R82.2, R84.2, R86.2, R89.2, R91.2, R93.2, R94.2, R96.2, R97.2, R99.2, R100.2, R102.2, R105.2, R108.2, R109.2, SW1.2, SW2.2, SW3.2, SW4.2, SW5.2, U1.7, U1.9, U2.1, U3.1, U3.40, U3.41, U4.2, U5.2, U6.5, U7.4, U8.2, U8.3, U8.12, U9.3, U9.9, U9.14, U9.16, U9.19, U9.23, U9.29, U9.38, U9.39, U9.40, U9.41, U9.42, U9.48, U10.1, U10.2, U10.9, U10.16, U11.2, U11.3, U11.12, U11.21, U12.9, U13.9, U13.11, U13.13, U13.15, U14.9, U14.11, U14.13, U14.15, U15.1, U15.3, U16.4, U16.10, U17.4, U18.1, U18.3, U19.1, U19.3, U20.1, U20.3, U21.1, U21.3, U22.2, U23.5, U24.1, U24.3, U24.9, U24.10, Y1.2, Y1.4
I2C_SCL: J5.3, J8.14, J25.3, R18.2, U3.5, U6.8, U7.6, U8.22, U11.22, U15.10, U16.2, U22.3, U22.4
I2C_SDA: J5.4, J8.13, J25.2, R17.2, U3.4, U6.7, U7.5, U8.23, U11.23, U15.9, U16.3, U22.1, U22.6
LORA_CS: R41.2, U3.8, U10.15
LORA_DIO0: U3.9, U10.5
LORA_DIO1: U8.17, U10.6
LORA_RST: U8.5, U10.4
MODEM_PWRKEY: J8.7, U8.6
MODEM_RI: J8.10, R48.2, U3.29
MODEM_RST: J8.8, U8.7
MODEM_RXD: J8.6, U3.36
MODEM_STATUS: J8.9, R47.1, U8.11
MODEM_TXD: J8.5, U3.37
ONEWIRE: R103.2, R104.1, U3.11
OUT1_CTL: R91.1, U3.23, U18.2
OUT2_CTL: R94.1, U3.25, U19.2
OUT3_CTL: R97.1, U3.15, U20.2
OUT4_CTL: R100.1, U3.26, U21.2
RS485A_DE: R105.1, U3.33, U23.2, U23.3
RS485A_RX: U3.32, U23.1
RS485A_TX: U3.31, U23.4
RS485B_DE: R109.1, U3.24, U24.5, U24.6
RS485B_RX: U3.35, U24.4
RS485B_TX: U3.34, U24.7
SD_CD: J7.10, R46.2, U8.10
SD_CS: J7.2, R42.2, U3.10
SPI_MISO: J7.7, R43.2, U3.19, U9.34, U10.13
SPI_MOSI: J7.3, U3.18, U9.35, U10.14
SPI_SCK: J7.5, U3.17, U9.33, U10.12
VBUS_USB: C25.1, D6.2, J3.A4, J3.A9, J3.B4, J3.B9, U4.5
VFIELD: C3.1, C65.1, D29.1, D30.1, D31.1, D32.1, F3.2, J22.1, J23.1, J26.1, U17.8
VIN_BAT_SENSE: C6.1, R3.2, R4.1, U3.38
VIN_MAIN_SENSE: C5.1, R1.2, R2.1, U3.39
VSENS: C4.1, F4.2, J19.1, J20.1

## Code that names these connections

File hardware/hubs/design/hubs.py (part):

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    mc.block("ESP32-WROOM-32E")
    # GPIOs are chosen by where the parts sit: the module's right column faces the RS-485 / uplink
    # blocks, its left column the power and front-panel side, its bottom row the charger.
    pins = {"VDD": "+3V3", "GND": "GND", "EN": "ESP_EN", "IO0": "BOOT_BTN", "TXD0/IO1": "ESP_TXD0",
            "RXD0/IO3": "ESP_RXD0", "IO2": "BUZZER_CTL", "IO13": "CHRG_N",
            "IO33": "I2C_SDA", "IO32": "I2C_SCL", "IO27": "LED_DATA",
            "IO34": "VBAT_ADC", "IO35": "VIN_ADC",
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               "SENSOR_VP", "SENSOR_VN"):
        pins[io] = NC
    if used["LORA"] or used["ETH"]:
        pins.update({"IO18": "SPI_SCK", "IO19": "SPI_MISO", "IO23": "SPI_MOSI"})
    if used["LORA"]:
        pins.update({"IO5": "LORA_CS", "IO21": "LORA_DIO0"})
        pins["IO14" if used["ETH"] else "IO22"] = "LORA_RST"
    if used["ETH"]:
        pins.update({"IO22": "ETH_CS", "SENSOR_VP": "ETH_INT"})
    if used["LTE"]:
        pins.update({"IO19": "MODEM_RXD", "IO23": "MODEM_TXD", "IO21": "MODEM_PWRKEY_CTL",
                     "IO22": "MODEM_EN", "IO18": "MODEM_STATUS"})
    mc.part("RF_Module:ESP32-WROOM-32E", "U", "ESP32-WROOM-32E-N8", "agrinode:ESP32-WROOM-32E_Coarse").c(pins)
    C(mc, "22u", "+3V3")
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             "VCAP": "ETH_VCAP", "RBIAS": "ETH_RBIAS", "OSC1": "ETH_OSC1", "OSC2": "ETH_OSC2",
             "~{CS}": "ETH_CS", "SCK": "SPI_SCK", "SI": "SPI_MOSI", "SO": "SPI_MISO", "~{INT}": "ETH_INT",
             "~{RESET}": "ESP_EN", "CLKOUT": NC, "~{WOL}": NC,
             "TPOUT+": "ETH_TXP", "TPOUT-": "ETH_TXN", "TPIN+": "ETH_RXP", "TPIN-": "ETH_RXN",
             "LEDA": "ETH_LEDA", "LEDB": "ETH_LEDB"})
        C(cm, "10u", "ETH_VCAP")
        R(cm, "2.32k 1%", "ETH_RBIAS", "GND")
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
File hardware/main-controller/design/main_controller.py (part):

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terminal_hdr.c({"1": "+3V3", "2": "EXP_IO5", "3": "EXP_IO6", "4": "EXP_IO7", "5": "GND"})

mc.block("Front panel: buttons, LEDs, buzzer, OLED")
for net, label in (("BTN_UP", "UP"), ("BTN_DOWN", "DOWN"), ("BTN_BACK", "BACK")):
    R(mc, "10k", "+3V3", net)
    mc.part("Switch:SW_Push", "SW", label, BTN).c({"1": net, "2": "GND"})
LED(mc, "blue STATUS", "LED_STATUS_A", "GND")
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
